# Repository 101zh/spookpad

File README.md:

# Spookpad

A 3x3 macropad made with the help of [Hack Club](https://hackclub.com/)'s [Hackpad](https://hackpad.hackclub.com) program.\
There are 8 keys that are backlit with LEDs, a rotary encoder, an OLED screen, and a XIAO RP2040 as the microcontroller.

https://github.com/user-attachments/assets/52a98100-4cb5-45ce-95d2-a7054d29ba24

## CAD

The case fits together using four M3 bolts and four M3 heatset inserts.\
The case is made of three separate printed pieces.\
The PCB just floats inside the 3D printed case. I would suggest that some insulation or some other material is placed inside, so that the PCB can be properly supported, instead of being supported by the sautered joints.

## PCB

The PCB was created in KiCad. The silkscreen images were imported using KiCad's image converter.

### Schematic

#### PCB With Zones

#### PCB Without Zones

## Firmware

This macropad uses [QMK](https://docs.qmk.fm/) for firmware.

- Rotary encoder knob adjusts the volume.
- By default, each key is bound to type out a number. The keys can type out the numbers 1 through 9. (There aren't enough keys to type out the number 0)
- This macropad is compatible with [VIA](https://caniusevia.com/), so that it can actually macro.
- The OLED screen should play the animation below at all times\

  - Still playing with the idea of displaying useful information.

## Bill of Materials (BOM)

Physical materials needed to make this macropad:

- 8x Cherry MX Switches
- 8x DSA Keycaps
- 1x EC11 Rotary Encoder
- 9x Through-hole 1N4148 Diodes
- 9x SK6812 MINI LEDs
- 4x M3x16mm Screws
- 4x M3x5mx4mm Heatset Inserts
- 1x 0.91" OLED Display
- 1x Seeed Studio XIAO RP2040
- 1x 3D printed knob for the rotary encoder
- 1x 3D printed case (3 separate pieces)

## Copyright

Copyright (C) 2025 101zh

This Source Code Form is subject to the terms of the Mozilla Public License, v. 2.0. If a copy of the MPL was not distributed with this file, You can obtain one at <https://mozilla.org/MPL/2.0/>.

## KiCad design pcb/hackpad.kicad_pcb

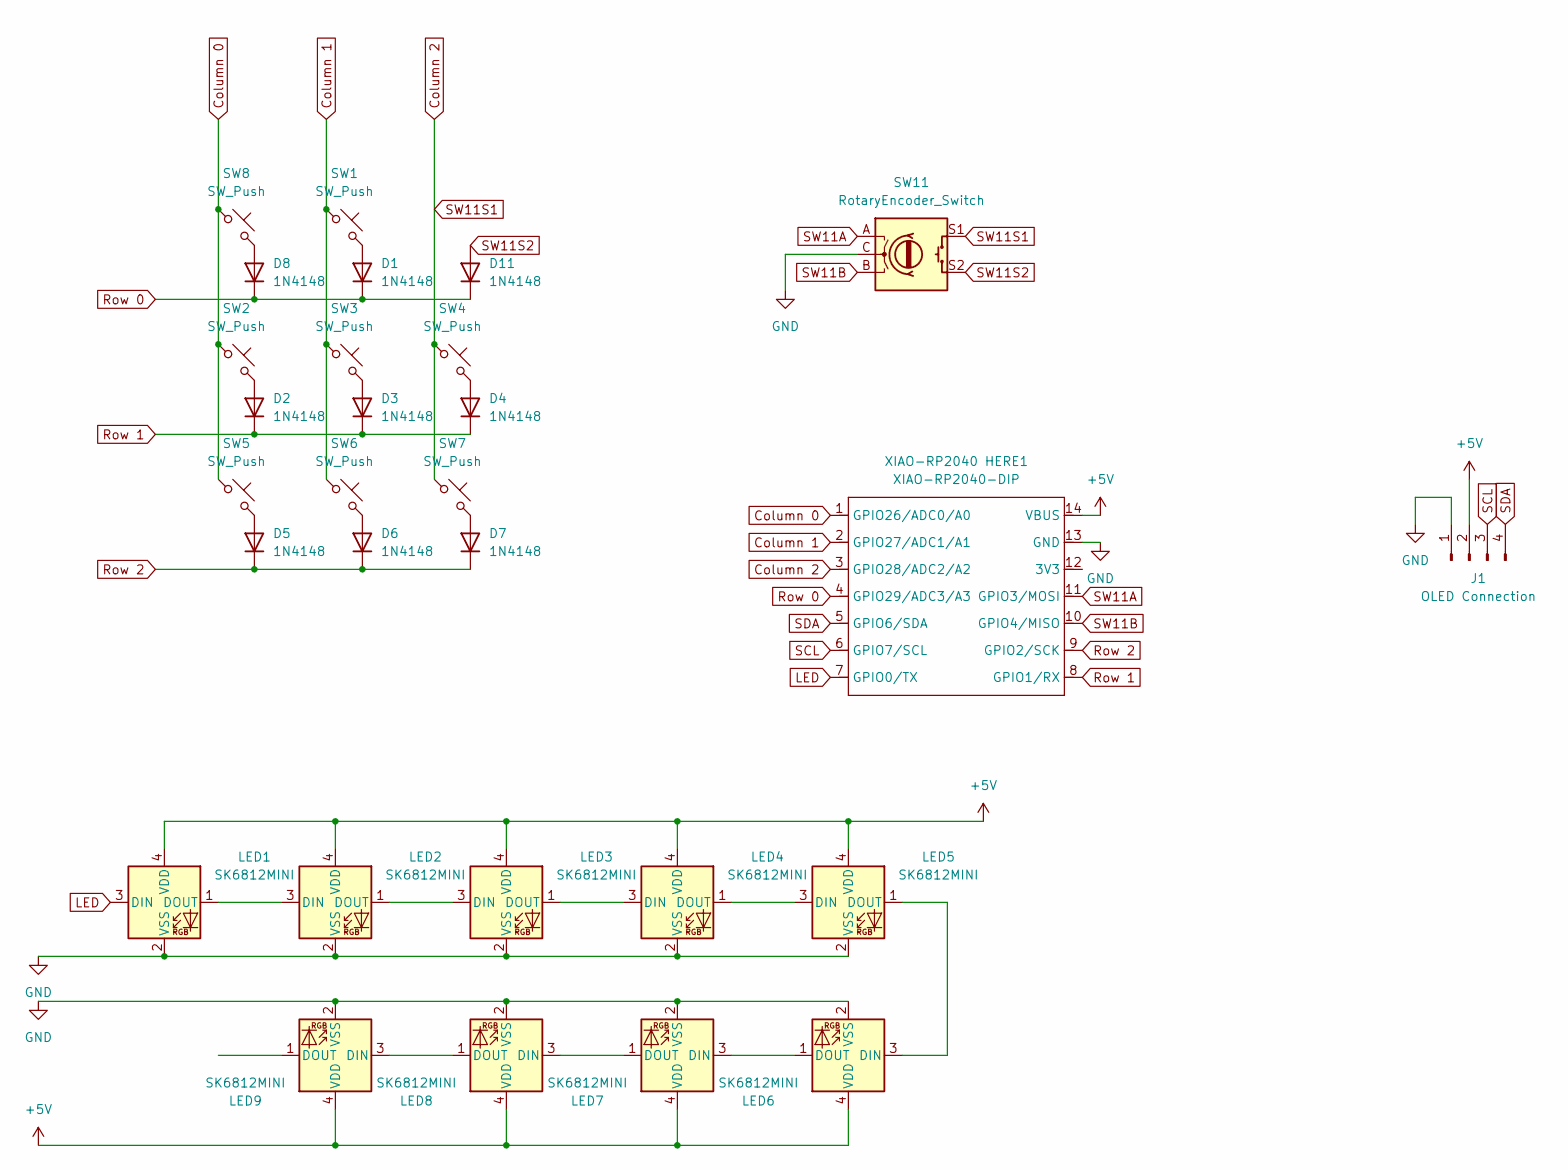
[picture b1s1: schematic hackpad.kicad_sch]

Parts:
D1, D2, D3, D4, D5, D6, D7, D8, D11: 1N4148; D_DO-35_SOD27_P7.62mm_Horizontal
J1: OLED Connection; 0.91-OLED-4pin
LED1, LED2, LED3, LED4, LED5, LED6, LED7, LED8, LED9: SK6812MINI; LED_SK6812MINI
SW1, SW2, SW3, SW4, SW5, SW6, SW7, SW8: SW_Push; SW_Cherry_MX_1.00ul
SW11: RotaryEncoder_Switch; RotaryEncoder_Alps_EC11E-Switch
XIAO-RP2040 HERE1: XIAO-RP2040-DIP; XIAO-RP2040-DIP_3D_Model

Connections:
+5V: J1.2, LED1.4 (VDD), LED2.4 (VDD), LED3.4 (VDD), LED4.4 (VDD), LED5.4 (VDD), LED6.4 (VDD), LED7.4 (VDD), LED8.4 (VDD), LED9.4 (VDD), XIAO-RP2040 HERE1.14 (VBUS)
Column 0: SW2.1, SW5.1, SW8.1, XIAO-RP2040 HERE1.1 (GPIO26/ADC0/A0)
Column 1: SW1.1, SW3.1, SW6.1, XIAO-RP2040 HERE1.2 (GPIO27/ADC1/A1)
Column 2: SW4.1, SW7.1, SW11.S1, XIAO-RP2040 HERE1.3 (GPIO28/ADC2/A2)
GND: J1.1, LED1.2 (VSS), LED2.2 (VSS), LED3.2 (VSS), LED4.2 (VSS), LED5.2 (VSS), LED6.2 (VSS), LED7.2 (VSS), LED8.2 (VSS), LED9.2 (VSS), SW11.C, XIAO-RP2040 HERE1.13 (GND)
LED: LED1.3 (DIN), XIAO-RP2040 HERE1.7 (GPIO0/TX)
unnamed: D1.2 (A), SW1.2
unnamed: D2.2 (A), SW2.2
unnamed: D3.2 (A), SW3.2
unnamed: D4.2 (A), SW4.2
unnamed: D5.2 (A), SW5.2
unnamed: D6.2 (A), SW6.2
unnamed: D7.2 (A), SW7.2
unnamed: D8.2 (A), SW8.2
unnamed: LED1.1 (DOUT), LED2.3 (DIN)
unnamed: LED2.1 (DOUT), LED3.3 (DIN)
unnamed: LED3.1 (DOUT), LED4.3 (DIN)
unnamed: LED4.1 (DOUT), LED5.3 (DIN)
unnamed: LED5.1 (DOUT), LED6.3 (DIN)
unnamed: LED6.1 (DOUT), LED7.3 (DIN)
unnamed: LED7.1 (DOUT), LED8.3 (DIN)
unnamed: LED8.1 (DOUT), LED9.3 (DIN)
Row 0: D1.1 (K), D8.1 (K), D11.1 (K), XIAO-RP2040 HERE1.4 (GPIO29/ADC3/A3)
Row 1: D2.1 (K), D3.1 (K), D4.1 (K), XIAO-RP2040 HERE1.8 (GPIO1/RX)
Row 2: D5.1 (K), D6.1 (K), D7.1 (K), XIAO-RP2040 HERE1.9 (GPIO2/SCK)
SCL: J1.3, XIAO-RP2040 HERE1.6 (GPIO7/SCL)
SDA: J1.4, XIAO-RP2040 HERE1.5 (GPIO6/SDA)
SW11A: SW11.A, XIAO-RP2040 HERE1.11 (GPIO3/MOSI)
SW11B: SW11.B, XIAO-RP2040 HERE1.10 (GPIO4/MISO)
SW11S2: D11.2 (A), SW11.S2

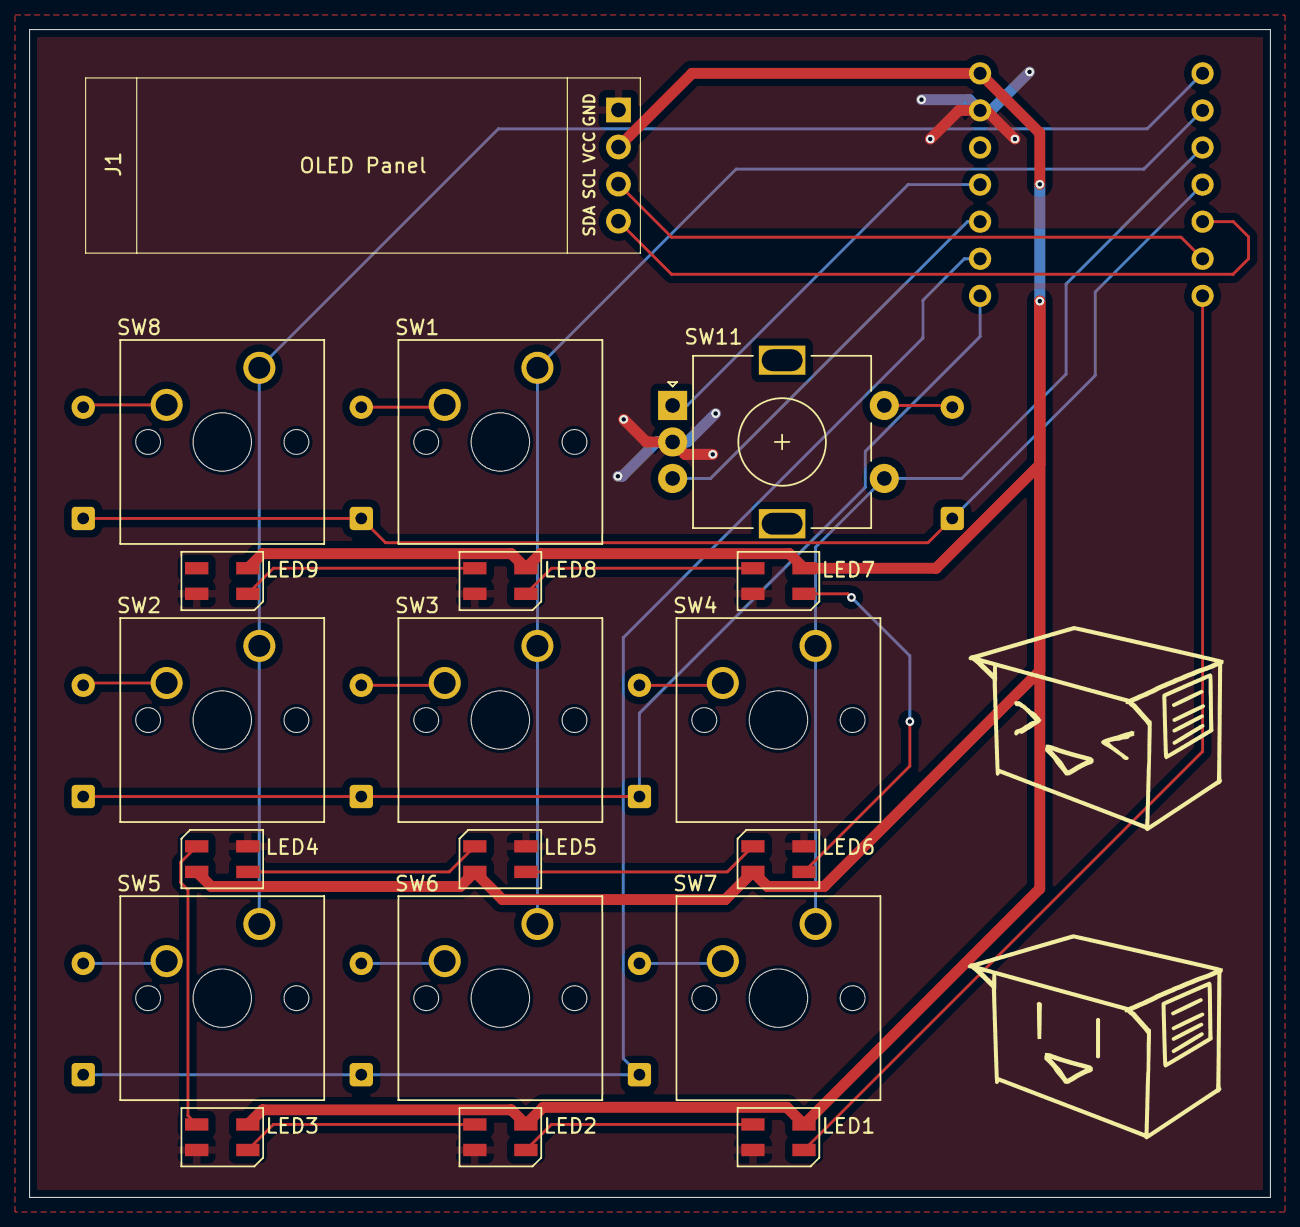
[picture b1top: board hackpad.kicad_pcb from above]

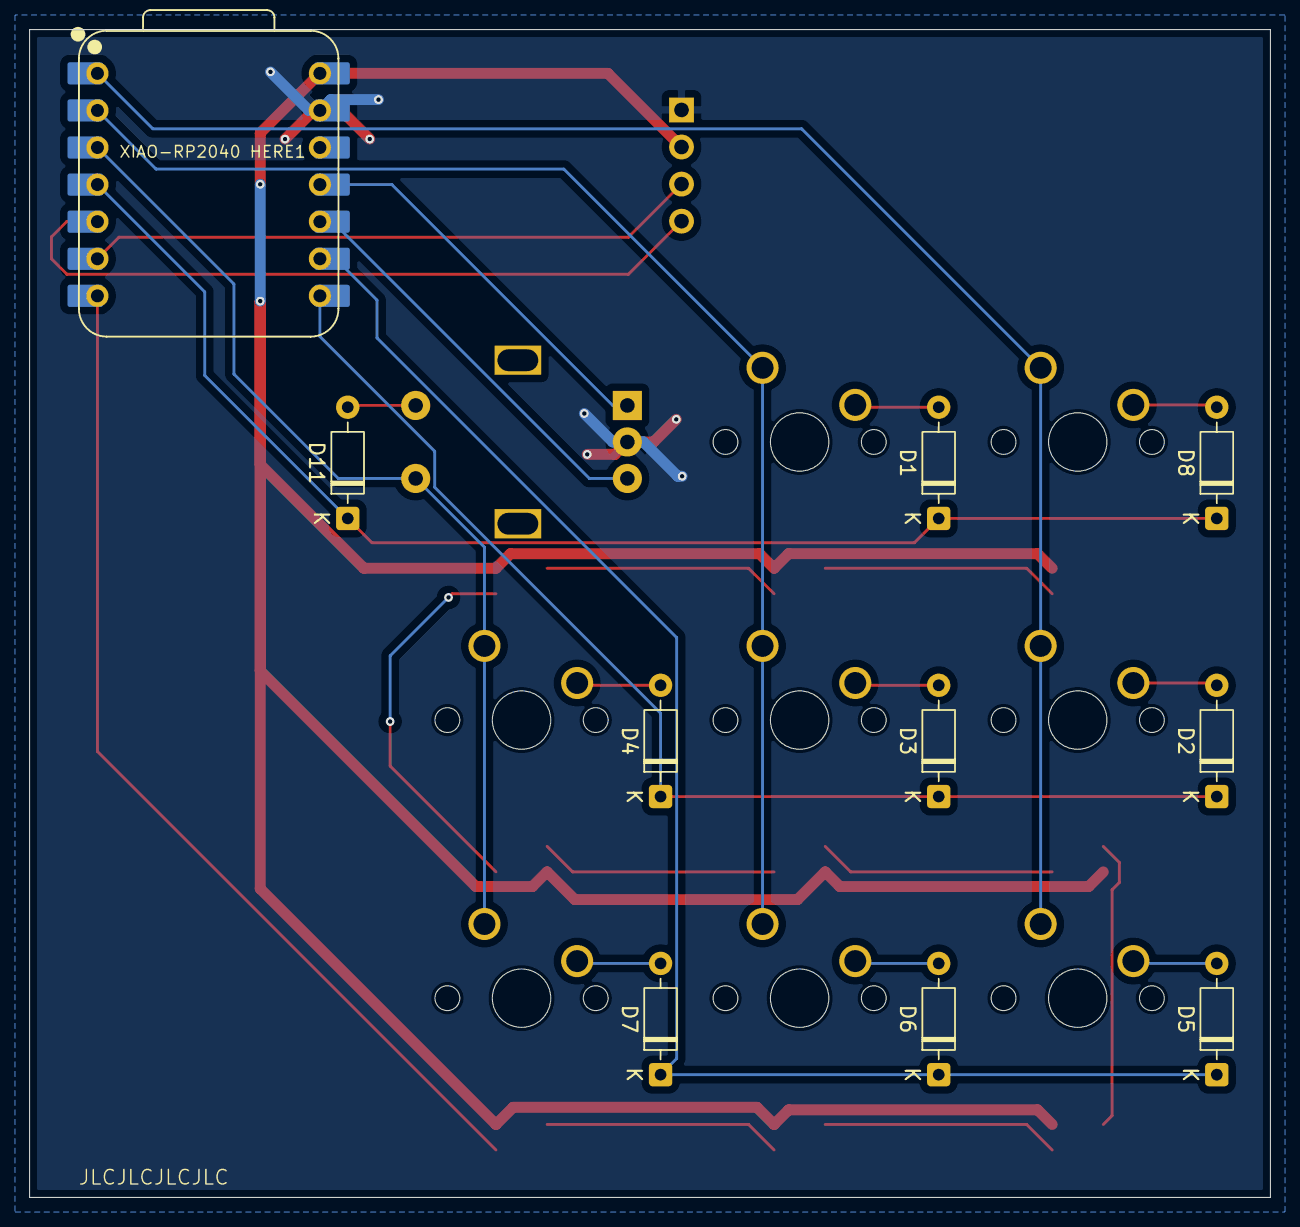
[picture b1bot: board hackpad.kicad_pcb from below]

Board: 2 copper layers, 85.0 x 80.0 mm, 29 parts (10 on the bottom side), 30 nets.

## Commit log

2025-05-21 create project
2025-05-24 brainstorm ideas for macropad
    - Why did this take so long...? (┬┬﹏┬┬)
2025-05-29 add wanted components in schematic
2025-05-29 add .gitignore file
2025-05-29 make .gitignore work
2025-05-31 finish schematic
2025-06-02 place keys and OLED screen in place
2025-06-02 finalize key and OLED screen placement
2025-06-03 route some pcb components
2025-06-03 redesign macropad
    - I just realized that I forgot the row pins 〒▽〒
2025-06-12 finish pcb
2025-06-17 add 3D models for footprints
2025-06-17 adjust edge cuts and 3D models
2025-06-18 make changes according to advice
2025-06-24 add images that are on the case
2025-06-24 update 3D model of pcb with small adjustments
2025-06-27 reorganize for hackpad submission
2025-06-27 add production files
2025-06-27 edit firmware
2025-06-30 code animation for firmware
2025-06-30 edit pcb
2025-06-30 add license
2025-06-30 edit README for readability
2025-06-30 prepare pcb for ordering
2025-07-01 add drill files to gerbers.zip
2025-07-01 adjust top case
    - adjusted so that it can be 3D printed
    - also adjusted, so that images aren't too small
2025-07-31 fix firmware
2025-08-19 add real-life image and video
2025-08-19 add video to README
